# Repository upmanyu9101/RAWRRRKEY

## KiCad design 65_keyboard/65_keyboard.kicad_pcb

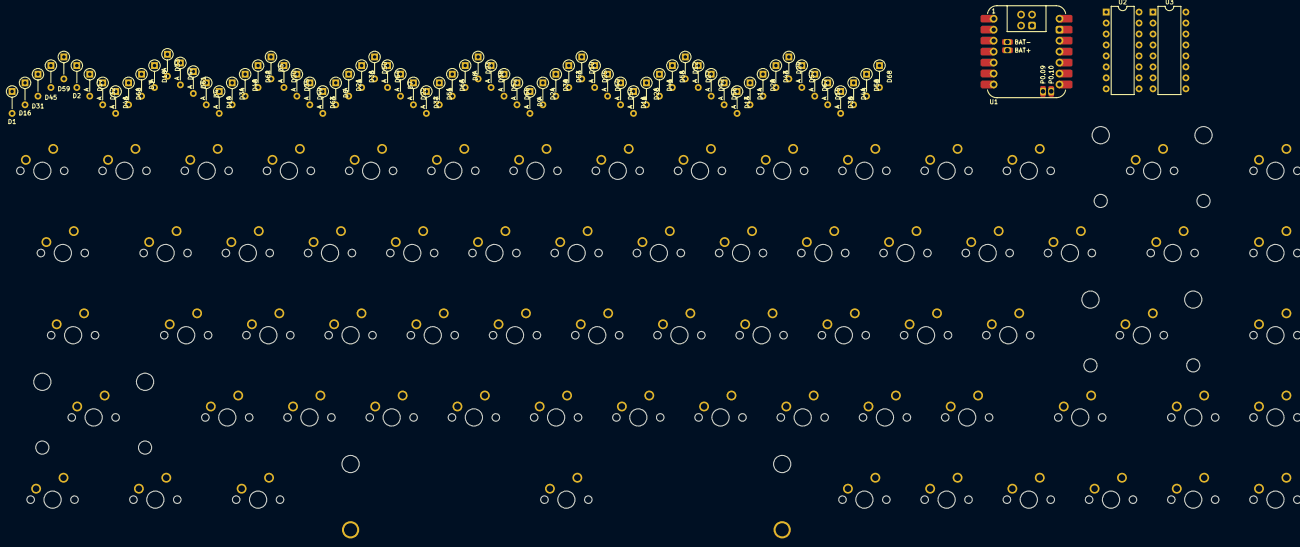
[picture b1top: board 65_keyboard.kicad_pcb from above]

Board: 2 copper layers, 143 parts (0 on the bottom side), 74 nets, no tracks yet.

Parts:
D1, D2, D3, D4, D5, D6, D7, D8, D9, D10, D11, D12, D13, D14, D15, D16, D17, D18, D19, D20, D21, D22, D23, D24, D25, D26, D27, D28, D29, D30, D31, D32, D33, D34, D35, D36, D37, D38, D39, D40, D41, D42, D43, D44, D45, D46, D47, D48, D49, D50, D51, D52, D53, D54, D55, D56, D57, D58, D59, D60, D61, D62, D63, D64, D65, D66, D67, D68: D; D_DO-35_SOD27_P5.08mm_Vertical_AnodeUp
S1: MX_stab; STAB_MX_P_6.25u
S2, S5, S6: MX_stab; STAB_MX_2u
SW1, SW2, SW3, SW4, SW5, SW6, SW7, SW8, SW9, SW10, SW11, SW12, SW13, SW14, SW15, SW16, SW17, SW18, SW19, SW20, SW21, SW22, SW23, SW24, SW25, SW26, SW27, SW28, SW29, SW30, SW31, SW32, SW33, SW34, SW35, SW36, SW37, SW38, SW39, SW40, SW41, SW42, SW43, SW44, SW45, SW46, SW47, SW48, SW49, SW50, SW51, SW52, SW53, SW54, SW55, SW56, SW57, SW58, SW59, SW60, SW61, SW62, SW63, SW64, SW65, SW66, SW67, SW68: MX_SW_solder; SW_MX_1u
U1: Seeeduino Xiao nRF52840; Xiao_nRF52840_ACH
U2, U3: 74HC595; DIP-16_W7.62mm

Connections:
+5V: U1.8 (5V), U2.10 (~SRCLR), U2.16 (VCC), U3.10 (~SRCLR), U3.16 (VCC)
D1: U1.2 (P0.03), U2.12 (RCLK), U3.12 (RCLK)
GND: U1.9 (GND), U2.8 (GND), U2.13 (~OE), U3.8 (GND), U3.13 (~OE)
unnamed: D1.2 (A), SW1.2
unnamed: D2.1 (K), SW2.2
unnamed: D3.2 (A), SW3.2
unnamed: D4.2 (A), SW4.2
unnamed: D5.2 (A), SW5.2
unnamed: D6.2 (A), SW6.2
unnamed: D7.2 (A), SW7.2
unnamed: D8.2 (A), SW8.2
unnamed: D9.2 (A), SW9.2
unnamed: D10.2 (A), SW10.2
unnamed: D11.2 (A), SW11.2
unnamed: D12.2 (A), SW12.2
unnamed: D13.2 (A), SW13.2
unnamed: D14.2 (A), SW14.2
unnamed: D15.2 (A), SW15.2
unnamed: D16.2 (A), SW16.2
unnamed: D17.2 (A), SW17.2
unnamed: D18.2 (A), SW18.2
unnamed: D19.2 (A), SW19.2
unnamed: D20.2 (A), SW20.2
unnamed: D21.2 (A), SW21.2
unnamed: D22.2 (A), SW22.2
unnamed: D23.2 (A), SW23.2
unnamed: D24.2 (A), SW24.2
unnamed: D25.2 (A), SW25.2
unnamed: D26.2 (A), SW26.2
unnamed: D27.2 (A), SW27.2
unnamed: D28.2 (A), SW28.2
unnamed: D29.2 (A), SW29.2
unnamed: D30.2 (A), SW30.2
unnamed: D31.2 (A), SW31.2
unnamed: D32.2 (A), SW32.2
unnamed: D33.2 (A), SW33.2
unnamed: D34.2 (A), SW34.2
unnamed: D35.2 (A), SW35.2
unnamed: D36.2 (A), SW36.2
unnamed: D37.2 (A), SW37.2
unnamed: D38.2 (A), SW38.2
unnamed: D39.2 (A), SW39.2
unnamed: D40.2 (A), SW40.2
unnamed: D41.2 (A), SW41.2
unnamed: D42.2 (A), SW42.2
unnamed: D43.2 (A), SW43.2
unnamed: D44.2 (A), SW44.2
unnamed: D45.2 (A), SW45.2
unnamed: D46.2 (A), SW46.2
unnamed: D47.2 (A), SW47.2
unnamed: D48.2 (A), SW48.2
unnamed: D49.2 (A), SW49.2
unnamed: D50.2 (A), SW50.2
unnamed: D51.2 (A), SW51.2
unnamed: D52.2 (A), SW52.2
unnamed: D53.2 (A), SW53.2
unnamed: D54.2 (A), SW54.2
unnamed: D55.2 (A), SW55.2
unnamed: D56.2 (A), SW56.2
unnamed: D57.2 (A), SW57.2
unnamed: D58.2 (A), SW58.2
unnamed: D59.2 (A), SW59.2
unnamed: D60.2 (A), SW60.2
unnamed: D61.2 (A), SW61.2
unnamed: D62.2 (A), SW62.2
unnamed: D63.2 (A), SW63.2
unnamed: D64.2 (A), SW64.2
unnamed: D65.2 (A), SW65.2
unnamed: D66.2 (A), SW66.2
unnamed: D67.2 (A), SW67.2
unnamed: D68.2 (A), SW68.2
unnamed: U1.11 (P1.15), U2.14 (SER)
unnamed: U2.9 (QH'), U3.14 (SER)
SCK: U1.13 (P1.13), U2.11 (SRCLK), U3.11 (SRCLK)

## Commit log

2024-09-07 did some stuff
2024-09-17 Done with schematics
